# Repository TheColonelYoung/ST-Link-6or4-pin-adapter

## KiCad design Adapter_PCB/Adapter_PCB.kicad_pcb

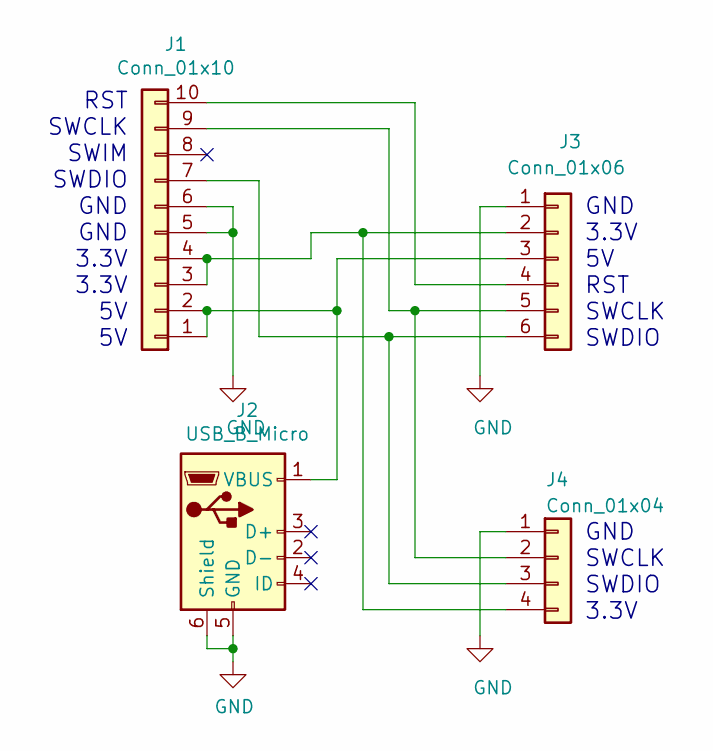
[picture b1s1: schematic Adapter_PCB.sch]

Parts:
J1: Conn_01x10; IDC-Header_2x05_P2.54mm_Horizontal
J2: USB_B_Micro; USB_Micro-B_Molex_47346-0001
J3: Conn_01x06; IDC-Header_2x03_P2.54mm_Horizontal
J4: Conn_01x04; PinHeader_1x04_P2.54mm_Horizontal

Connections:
GND: J1.5, J1.6, J2.5 (GND), J2.6 (Shield), J3.1, J4.1
unnamed: J1.1, J1.2, J2.1 (VBUS), J3.3
unnamed: J1.3, J1.4, J3.2, J4.4
unnamed: J1.7, J3.6, J4.3
unnamed: J1.9, J3.5, J4.2
unnamed: J1.10, J3.4

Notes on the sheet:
GND 3.3V 5V RST SWCLK SWDIO
GND SWCLK SWDIO 3.3V
RST SWCLK SWIM SWDIO GND GND 3.3V 3.3V 5V 5V

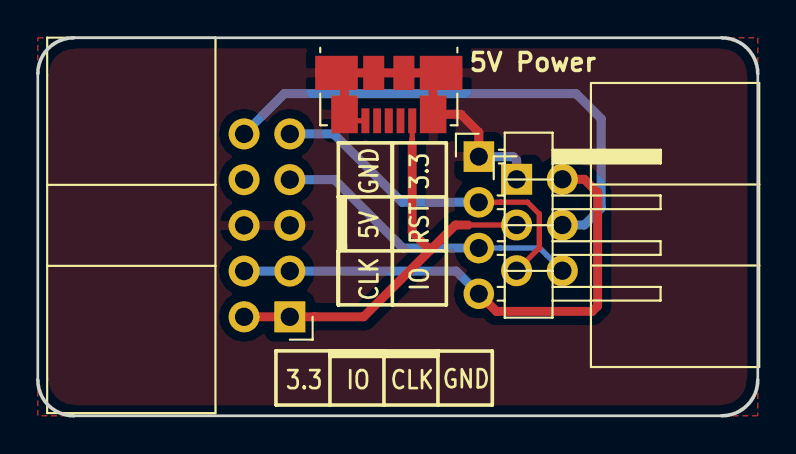
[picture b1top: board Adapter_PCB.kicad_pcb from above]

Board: 2 copper layers, 40.0 x 21.0 mm, 4 parts (0 on the bottom side), 6 nets.

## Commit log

2019-02-08 Created schema and first draft of PCB
2019-02-11 Add 4 pin connector, change connector pinout, add silkscreen
    Only one of reducing connectors can be populated.
    In silkscreen are now connector pinouts diagrams and logo with QR code.
    Connector pinout was rearranged to mach IDC cable with lock on different sides.
2019-02-11 Add panelized version of PCB (2x3)
2019-02-11 Add .zip with gerber files for fabrication
2019-02-11 Update PCB, change QR to match correct repository address
